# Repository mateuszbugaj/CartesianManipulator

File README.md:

# CartesianManipulator
This repository contains the firmware for a three-axis manipulator system. The manipulator utilizes three stepper motors controlled by A4988 stepper motor drivers. This project is designed for AVR microcontrollers.

## Overview
The manipulator has three axes: X, Y, and Z, each controlled by a stepper motor. Each axis also has an edge switch to determine its limit. The project code includes routines for handling move commands, speed changes, precision and normal mode, and homing.

Demo of the manipulator: [CartesianManipulatorDemo.gif](CartesianManipulatorDemo.gif) <br/><br/>

The project also includes a USART serial communication module and a basic command parser for controlling the manipulator. The manipulator can be controlled in relative or absolute positioning modes.

## Hardware
The hardware requirements for this project include:

1. AVR microcontroller
2. Three A4988 stepper motor drivers
3. Three stepper motors
4. Three edge switches
5. Gripper with servo motor

Files describing PCB layout can be found in `PCB/` directory.

## Software
The firmware is written in C and requires AVR GCC to compile.

Clone this repository to your local machine.
Open the project in your AVR development environment.
Build the project and flash the compiled firmware onto your AVR microcontroller.

```bash
make && make flash
```

## Usage
You can control the manipulator via USART using the following commands:

1. G0 \<X> \<Y> \<Z> : Move the manipulator to the specified position.
2. G28 : Home the manipulator.
3. F \<S> : Change the speed of the manipulator.
4. PREC : Switch the manipulator to precision mode.
5. NORM : Switch the manipulator to normal mode.
6. M \<G> : Control the gripper openness.
7. ZERO : Zero the manipulator's position.
8. LIMITX \<L> \<U> : Set the lower and upper limits for the X axis.
9. LIMITY \<L> \<U> : Set the lower and upper limits for the Y axis.
10. LIMITZ \<L> \<U> : Set the lower and upper limits for the Z axis.
11. G90 : Switch to relative positioning mode.
12. G91 : Switch to absolute positioning mode.

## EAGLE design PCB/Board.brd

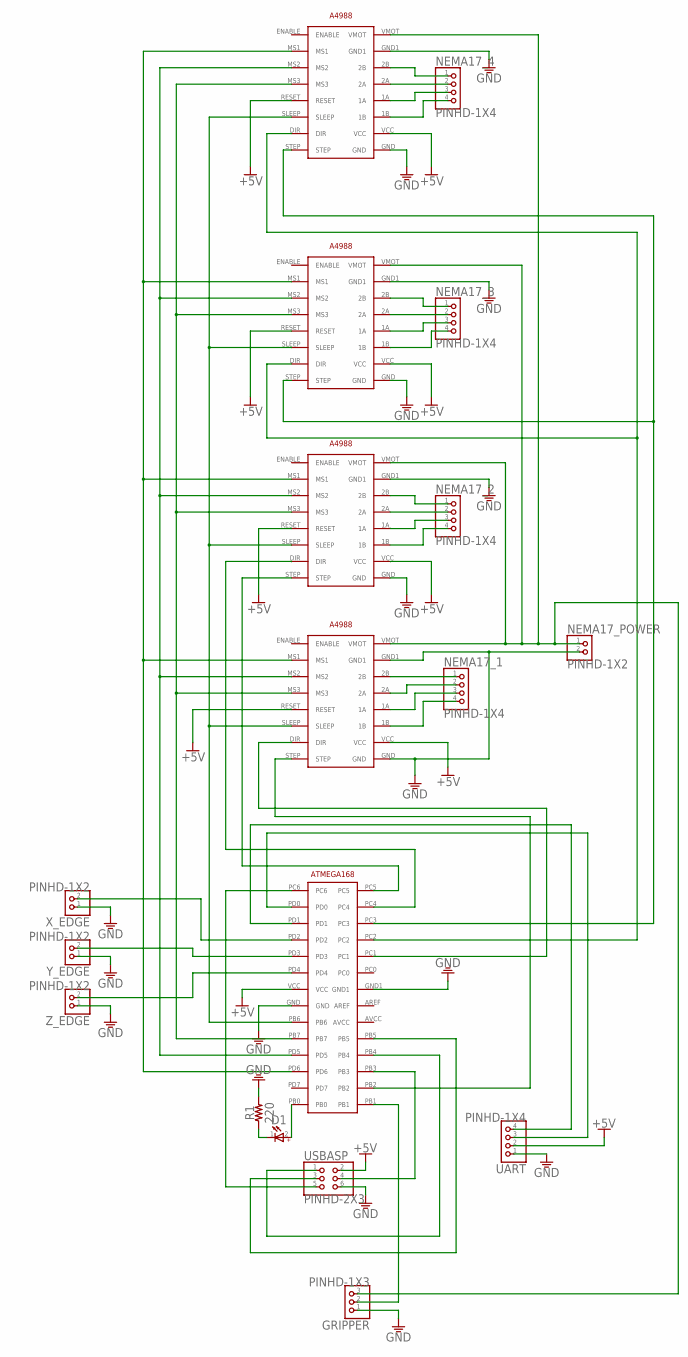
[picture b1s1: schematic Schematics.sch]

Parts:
D1: 151033BS03000; WL-TMRW_3MM_STOPPER
GRIPPER: PINHD-1X3; 1X03
NEMA17_1, NEMA17_2, NEMA17_3, NEMA17_4: PINHD-1X4; 1X04
NEMA17_POWER: PINHD-1X2; 1X02
R1: 220; RESAD724W46L381D178B
U$1: ATMEGA168; ATMEGA168FOOTPRINT
U$2, U$3, U$4, U$5: A4988; A498-FOOTPRINT
UART: PINHD-1X4; 1X04
USBASP: PINHD-2X3; 2X03
X_EDGE: PINHD-1X2; 1X02
Y_EDGE: PINHD-1X2; 1X02
Z_EDGE: PINHD-1X2; 1X02

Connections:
+5V: U$1.VCC, U$2.RESET, U$2.VCC, U$3.RESET, U$3.VCC, U$4.RESET, U$4.VCC, U$5.RESET, U$5.VCC, UART.2, USBASP.2
GND: GRIPPER.1, NEMA17_POWER.2, R1.2, U$1.GND, U$1.GND1, U$2.GND, U$2.GND1, U$3.GND, U$3.GND1, U$4.GND, U$4.GND1, U$5.GND, U$5.GND1, UART.1, USBASP.6, X_EDGE.1, Y_EDGE.1, Z_EDGE.1
unnamed: U$1.PB3, USBASP.4
unnamed: U$1.PB4, USBASP.1
unnamed: U$1.PB5, USBASP.3
unnamed: U$1.PC6, USBASP.5
unnamed: D1.2 (+), U$1.PB0
unnamed: D1.1 (-), R1.1
unnamed: U$1.PD0, UART.3
unnamed: U$1.PD1, UART.4
unnamed: NEMA17_1.1, U$2.2B
unnamed: NEMA17_1.2, U$2.2A
unnamed: NEMA17_1.3, U$2.1A
unnamed: NEMA17_1.4, U$2.1B
unnamed: U$1.PB2, U$2.STEP
unnamed: GRIPPER.3, NEMA17_POWER.1, U$2.VMOT, U$3.VMOT, U$4.VMOT, U$5.VMOT
unnamed: U$1.PC1, U$2.DIR
unnamed: U$1.PB6, U$2.SLEEP, U$3.SLEEP, U$4.SLEEP, U$5.SLEEP
unnamed: U$1.PB7, U$2.MS3, U$3.MS3, U$4.MS3, U$5.MS3
unnamed: U$1.PD5, U$2.MS2, U$3.MS2, U$4.MS2, U$5.MS2
unnamed: U$1.PD6, U$2.MS1, U$3.MS1, U$4.MS1, U$5.MS1
unnamed: NEMA17_2.4, U$3.1B
unnamed: NEMA17_2.3, U$3.1A
unnamed: NEMA17_2.2, U$3.2A
unnamed: NEMA17_2.1, U$3.2B
unnamed: U$1.PC5, U$3.STEP
unnamed: U$1.PC4, U$3.DIR
unnamed: NEMA17_3.4, U$4.1B
unnamed: NEMA17_3.3, U$4.1A
unnamed: NEMA17_3.2, U$4.2A
unnamed: NEMA17_3.1, U$4.2B
unnamed: U$1.PC3, U$4.STEP, U$5.STEP
unnamed: U$1.PC2, U$4.DIR, U$5.DIR
unnamed: NEMA17_4.4, U$5.1B
unnamed: NEMA17_4.3, U$5.1A
unnamed: NEMA17_4.2, U$5.2A
unnamed: NEMA17_4.1, U$5.2B
unnamed: U$1.PD2, X_EDGE.2
unnamed: U$1.PD3, Y_EDGE.2
unnamed: U$1.PD4, Z_EDGE.2
unnamed: GRIPPER.2, U$1.PB1

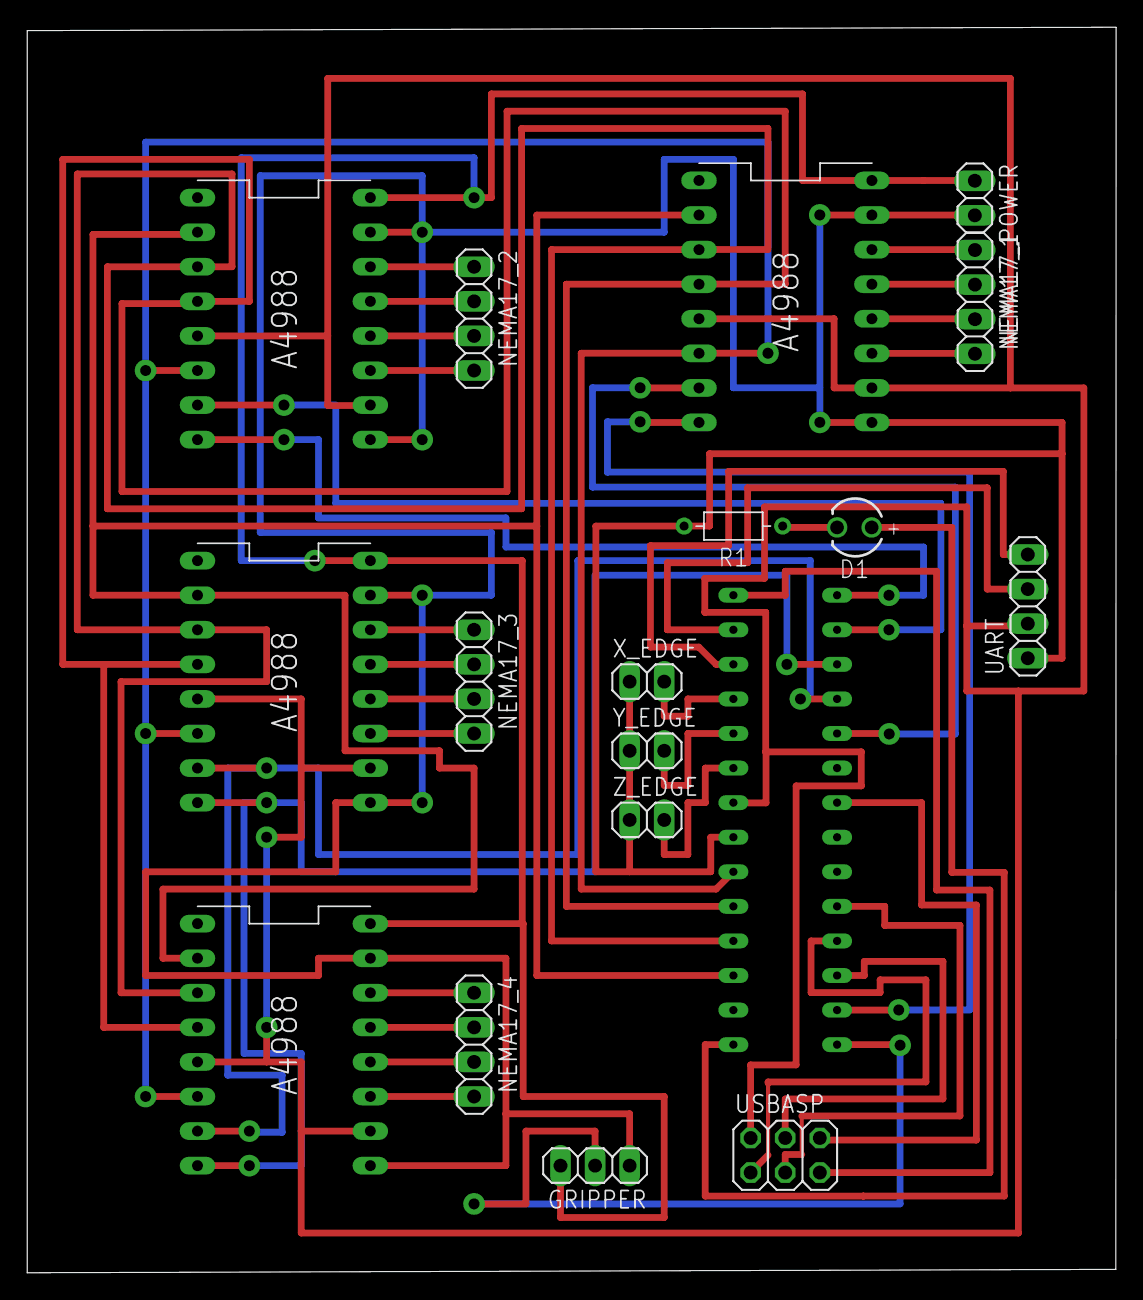
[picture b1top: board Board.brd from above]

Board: 2 copper layers, 80.0 x 91.5 mm, 18 parts (0 on the bottom side), 41 nets.

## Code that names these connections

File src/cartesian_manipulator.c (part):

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} Axis;

A4988 motor_x = {
    .step = { .port = &PORTC, .pin = PC1 },
    .dir = { .port = &PORTB, .pin = PB2 },
    .sleep = { .port = &PORTB, .pin = PB6},
    .ms1 = { .port = &PORTD, .pin = PD6},
    .ms2 = { .port = &PORTD, .pin = PD5},
    .ms3 = { .port = &PORTB, .pin = PB7}
};

A4988 motor_y = {
    .step = { .port = &PORTC, .pin = PC2 },
    .dir = { .port = &PORTC, .pin = PC3 },
    .sleep = { .port = &PORTB, .pin = PB6},
    .ms1 = { .port = &PORTD, .pin = PD6},
    .ms2 = { .port = &PORTD, .pin = PD5},
    .ms3 = { .port = &PORTB, .pin = PB7}
};

A4988 motor_z = {
    .step = { .port = &PORTC, .pin = PC4 },
    .dir = { .port = &PORTC, .pin = PC5 },
    .sleep = { .port = &PORTB, .pin = PB6},
    .ms1 = { .port = &PORTD, .pin = PD6},
    .ms2 = { .port = &PORTD, .pin = PD5},
    .ms3 = { .port = &PORTB, .pin = PB7}
};

GPIOPin edge_switch_x = { .port = &PORTD, .pin = PD2 };
GPIOPin edge_switch_y = { .port = &PORTD, .pin = PD3 };
GPIOPin edge_switch_z = { .port = &PORTD, .pin = PD4 };

Axis axis_x = { 
    .direction = 'x',
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    // Initialize gripper
    gripper_init();

	GPIOPin LED = { .port = &PORTB, .pin = PB0 };
	gpio_pin_direction(LED, OUTPUT);

    usart_print("Cartesian Manipulator start...\n\r");
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
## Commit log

2023-05-26 Initial
2023-05-26 Add A4988 Controller submodule
2023-05-26 Updated StepperMotorDriver library submodule
2023-05-26 Makefile
2023-05-27 Initial knob example
2023-05-27 Added X and Y axis moving, modified parser to handle commands with multiple float params
2023-05-27 Removed the fauilty X/Y synchronization for now
2023-05-28 A4988Controller uplift
2023-05-28 Makefile fix
2023-05-28 Initial homing command
2023-05-31 Clearing parser context after command, working homing, removed acceleration (we will get them next time)
2023-06-02 Added gripper support
2023-06-03 Added limits and positioning
2023-06-03 Added Z axis
2023-06-03 4988Controller Uplift
2023-06-03 Fixed homing
2023-06-12 Added command to set the z axis limit
2023-07-21 Modified axisy.zero_after_homing
2023-07-27 Fixed Z axis movement confirmation, no axis moves if one is out of bounds, NORMAL_SPEED adjusted
2023-08-01 Added Z axis speed adjustment
2023-09-11 PCB and README
2023-09-15 README

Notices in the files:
parts and their libraries:
Wurth_LEDs_WL-TMRW: Copyright: Würth Elektronik
